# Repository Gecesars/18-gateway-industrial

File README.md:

# EDGE-18 — Gateway Industrial Modbus/CAN Universal

Plataforma-pai para aquisição industrial e telemetria dos demais projetos do
portfólio. O EDGE-18 lê Modbus RTU, quatro sinais 0–10 V/4–20 mA e quatro
entradas digitais/pulso, conserva dados offline e publica por MQTT/TLS.

> **Estado: revisão digital A congelada para documentação — não fabricar.**
> O esquemático passa no ERC, mas a PCB foi mantida no ponto solicitado pelo
> responsável: 43 ocorrências de DRC e 24 conexões abertas. Os arquivos servem
> para revisão de engenharia e continuidade do desenvolvimento; não constituem
> uma liberação fabril, protótipo validado ou produto certificado.

## Arquitetura P0

| Bloco | Seleção |
|---|---|
| MCU | STM32H563ZIT6, Cortex-M33/TrustZone |
| Ethernet | LAN8742Ai, RMII 10/100 |
| Wi-Fi | ESP32-C3-MINI-1 opcional |
| RS-485 | 2 × ISOW1412 isoladas |
| Analógicas | ADS8684, quatro canais de 16 bits |
| Digitais | 2 × ISO1212, quatro entradas de 24 V |
| CAN | ISO1042 reservado para fase 2 |
| Alimentação | 9–36 Vcc; LM76002 como referência |
| PCB | 180 × 120 mm, quatro camadas |

O MVP é somente de monitoramento. Não possui saídas de comando e não substitui
CLP ou relé de segurança.

## Entregue nesta revisão

- requisitos verificáveis e seis ADRs;
- esquemático KiCad A0 com sete blocos e ERC limpo;
- PCB KiCad de quatro camadas, 180 × 120 mm, com roteamento parcial congelado;
- trilhas de 0,25 a 1,20 mm, sem segmento abaixo de 0,25 mm;
- BOM de 181 posições, pinout de 144 pinos e cálculos elétricos;
- STEP atual da PCB e conjunto paramétrico FreeCAD;
- relatório DRC integral com as pendências conhecidas;
- arquitetura elétrica e de software;
- contratos de configuração e telemetria em JSON Schema;
- exemplos válidos;
- núcleo C17 testável com configuração, Modbus, scheduler, journal, telemetria,
  máquina de estados e manifesto de atualização;
- testes estritos no host e CI;
- quinze vistas técnicas e PDF consolidado.

## Evidência CAD — 15 vistas

Os recortes do esquemático foram exportados em alta resolução e ampliados por
bloco para preservar referências, valores e nomes de redes. As vistas da PCB
mostram deliberadamente o estado congelado, inclusive o roteamento ainda
incompleto.

| | | |
|---|---|---|
|  |  |  |
|  |  |  |
|  |  |  |
|  |  |  |
|  |  |  |

Documento consolidado: [EDGE-18 — projeto completo Rev. A](docs/EDGE-18-projeto-completo-rev-a.pdf).

## Verificação local

```bash
./tools/run-checks.sh
```

## Navegação

- [índice técnico](docs/README.md);
- [requisitos](docs/01-requisitos.md);
- [arquitetura](docs/02-arquitetura.md);
- [hardware](docs/03-hardware.md);
- [software](docs/04-software.md);
- [estado congelado da PCB Rev. A](docs/17-estado-da-pcb-rev-a.md);
- [relatório ERC](docs/reports/edge18-main-rev-a-erc.rpt);
- [relatório DRC](docs/reports/edge18-main-rev-a-drc.rpt);
- [fontes primárias](docs/12-fontes-primarias.md);
- [status](project-management/STATUS.md);
- [roadmap](project-management/ROADMAP.md).

## Licença

A licença ainda não foi definida. Não redistribua artefatos como se uma licença
já tivesse sido concedida.

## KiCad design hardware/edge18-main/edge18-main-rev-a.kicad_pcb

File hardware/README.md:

# Hardware

## Finalidade

Fontes de eletrônica do projeto.

## Entregáveis Rev. A

- `edge18-main/edge18-main-rev-a.kicad_sch`: esquemático A0 com sete blocos;
- `edge18-main/edge18-main-rev-a.kicad_pcb`: PCB 180 × 120 mm, quatro camadas;
- `libraries/frozen/`: símbolos resolvidos e congelados para ERC reprodutível;
- `bom/edge18-main-rev-a-source.csv`: 181 posições e quatro DNP;
- `scripts/generate_kicad.py`: fonte determinística de esquemático, PCB inicial
  e BOM;
- `scripts/generate_pinout.py`: tabela dos 144 pinos extraída do CAD;
- `scripts/specctra_io.py`: intercâmbio DSN/SES;
- relatórios ERC/DRC em `docs/reports/`.

## Regras principais

- trilha mínima global: 0,25 mm;
- padrão: 0,30 mm; analógico: 0,35 mm; campo: 0,50 mm;
- alimentação: 0,80 mm; VIN: 1,20 mm;
- quatro camadas: F.Cu, In1.Cu, In2.Cu e B.Cu;
- três rasgos sob as barreiras isoladas;
- ESP32-C3-WROOM-02 marcado DNP;
- nenhuma saída de controle de processo.

## Estado congelado

A PCB Rev. A foi congelada em 27 de julho de 2026 com 43 ocorrências de DRC e
24 conexões abertas, por decisão do responsável. Não retome o roteamento nem
gere arquivos fabris a partir desta baseline sem nova autorização. O
esquemático tem ERC limpo e não há trilha abaixo de 0,25 mm.

Detalhes: [`../docs/17-estado-da-pcb-rev-a.md`](../docs/17-estado-da-pcb-rev-a.md).

## Regeneração e validação de desenvolvimento

```bash
./tools/generate-hardware.sh
./tools/kicad-cli.sh sch erc \
  --exit-code-violations hardware/edge18-main/edge18-main-rev-a.kicad_sch
./tools/kicad-cli.sh pcb drc \
  --exit-code-violations hardware/edge18-main/edge18-main-rev-a.kicad_pcb
```

`generate-hardware.sh` substitui o PCB pelo posicionamento inicial; execute o
roteamento depois dele somente em uma futura linha de desenvolvimento
autorizada. `--schematic-only` atualiza esquemático, BOM e bibliotecas sem tocar
na PCB congelada; `--bom-only` atualiza somente a BOM.

## Limite da liberação

O ERC está limpo, mas o DRC não está. A revisão atual não pode ser fabricada.
Protótipo, DFM, bring-up, térmica, surto, EMC e isolamento também continuam
pendentes.

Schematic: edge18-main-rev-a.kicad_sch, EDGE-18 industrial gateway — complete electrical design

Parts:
BT1: CR1220; BatteryHolder_Keystone_3000_1x12mm; MPN 3000
C1: 100uF 63V; C_1210_3225Metric; MPN X7R industrial equivalent
C2: 1uF 100V X7R; C_1210_3225Metric; MPN X7R industrial equivalent
C3: 100nF 100V; C_0603_1608Metric; MPN C1608 X7R series
C4, C5: 10uF 16V; C_0603_1608Metric; MPN C1608 X7R series
C6: 4.7nF; C_0603_1608Metric; MPN C1608 X7R series
C7, C8: 22uF 10V; C_0603_1608Metric; MPN C1608 X7R series
C9: 10nF; C_0603_1608Metric; MPN C1608 X7R series
C10: 10uF 10V; C_0603_1608Metric; MPN C1608 X7R series
C11, C12, C13, C14: 12pF C0G; C_0603_1608Metric; MPN C1608 series
C15, C16, C17, C18, C19, C20, C21, C22, C26, C28, C29: 100nF; C_0603_1608Metric; MPN C1608 series
C23: 4.7uF; C_0603_1608Metric; MPN C1608 series
C24, C25: 2.2uF low-ESR; C_0603_1608Metric; MPN C1608 series
C27: 1uF; C_0603_1608Metric; MPN C1608 series
C30, C31, C32, C43, C44, C65, C84, C85, C90, C92: 100nF; C_0603_1608Metric
C33: 1uF 10V; C_0603_1608Metric; MPN C1608 X7R series
C40, C41: 12pF C0G; C_0603_1608Metric
C42: 1uF; C_0603_1608Metric
C45, C64: 10uF; C_0603_1608Metric
C46: 10uF; C_0805_2012Metric; not fitted
C60, C61, C62, C63: 10nF C0G; C_0603_1608Metric; MPN C1608C0G1H103J080AA
C66, C67: 10uF low-ESR; C_0603_1608Metric
C80, C81, C82, C83: 10nF 100V; C_1206_3216Metric; MPN C3216X7R2A103K160AA
C91, C93: 2.2uF 10V; C_0805_2012Metric
C94: 100nF; C_0805_2012Metric
C95: 2.2uF; C_0805_2012Metric
D1: SMBJ36A; D_SMB; MPN SMBJ36A
D2: SS56 60V/5A; D_SMB; MPN SS56-13-F
D3: RUN GREEN; LED_0603_1608Metric; MPN 0603 green LED
D4: FAULT RED; LED_0603_1608Metric; MPN 0603 red LED
D10, D11, D12, D13: SMAJ12A; D_SMA; MPN SMAJ12A
D14, D15, D16, D17: SMAJ33A; D_SMA; MPN SMAJ33A
D18, D19, D20: SM712; SOT-23; MPN SM712-02HTG
F1: 2A resettable; Fuse_1812_4532Metric; MPN 1812L200/33
FB1, FB2, FB3: 600R@100MHz; L_0603_1608Metric; MPN BLM18AG601SN1D
J1: POWER 9–36V / RETURN / CHASSIS; TerminalBlock_Phoenix_MKDS-1,5-3-5.08_1x03_P5.08mm_Horizont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; MPN 1715035 equivalent
J2: ARM SWD 10-pin; PinHeader_2x05_P1.27mm_Vertical_SMD; MPN FTSH-105-01-L-DV-K
J3: MICROSD INDUSTRIAL; microSD_HC_Molex_104031-0811; MPN 104031-0811
J4: USB-C SERVICE DEVICE; USB_C_Receptacle_GCT_USB4105-xx-A_16P_TopMnt_Horizontal; MPN USB4105-GF-A
J5: RJ45 MAGJACK 10/100; RJ45_Hanrun_HR911105A_Horizontal; MPN HR911105A
J6: SERVICE / EXPANSION; PinHeader_1x08_P2.54mm_Vertical
J10: AI1 / AGND; TerminalBlock_Phoenix_MKDS-1,5-2-5.08_1x02_P5.08mm_Horizont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; MPN MKDS 1,5/2-5,08
J11: AI2 / AGND; TerminalBlock_Phoenix_MKDS-1,5-2-5.08_1x02_P5.08mm_Horizont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; MPN MKDS 1,5/2-5,08
J12: AI3 / AGND; TerminalBlock_Phoenix_MKDS-1,5-2-5.08_1x02_P5.08mm_Horizont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; MPN MKDS 1,5/2-5,08
J13: AI4 / AGND; TerminalBlock_Phoenix_MKDS-1,5-2-5.08_1x02_P5.08mm_Horizont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; MPN MKDS 1,5/2-5,08
J14: DI1 / DI2 / DI3 / DI4 / FIELD COM; TerminalBlock_Phoenix_MKDS-1,5-5-5.08_1x05_P5.08mm_Horizont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; MPN MKDS 1,5/5-5,08
J15: RS-485 A: A+ / B- / ISO GND; TerminalBlock_Phoenix_MKDS-1,5-3-5.08_1x03_P5.08mm_Horizont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; MPN MKDS 1,5/3-5,08
J16: RS-485 B: A+ / B- / ISO GND; TerminalBlock_Phoenix_MKDS-1,5-3-5.08_1x03_P5.08mm_Horizont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; MPN MKDS 1,5/3-5,08
J17: CAN-H / CAN-L / ISO GND; TerminalBlock_Phoenix_MKDS-1,5-3-5.08_1x03_P5.08mm_Horizont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; MPN MKDS 1,5/3-5,08
JP1: AI1 CURRENT MODE; SolderJumper-2_P1.3mm_Open_Pad1.0x1.5mm
JP2: AI2 CURRENT MODE; SolderJumper-2_P1.3mm_Open_Pad1.0x1.5mm
JP3: AI3 CURRENT MODE; SolderJumper-2_P1.3mm_Open_Pad1.0x1.5mm
JP4: AI4 CURRENT MODE; SolderJumper-2_P1.3mm_Open_Pad1.0x1.5mm
JP5, JP6: 120R TERMINATION ENABLE; SolderJumper-2_P1.3mm_Open_Pad1.0x1.5mm
JP7: CAN 120R TERMINATION; SolderJumper-2_P1.3mm_Open_Pad1.0x1.5mm
L1: 10uH input EMI; L_12x12mm_H6mm; MPN SRP1265A-100M
L2: 10uH / 4.5A; L_10.4x10.4_H4.8; MPN XAL1010-103
L3: 2.2uH / 4A; L_6.3x6.3_H3; MPN XFL6030-222
R1: 40.2k 1%; R_0603_1608Metric; MPN RC0603FR series
R2: 10.0k 1%; R_0603_1608Metric; MPN RC0603FR series
R3: 150k 1%; R_0603_1608Metric; MPN RC0603FR series
R4, R15: 33k 1%; R_0603_1608Metric; MPN RC0603FR series
R5, R16, R19: 100k 1%; R_0603_1608Metric; MPN RC0603FR series
R6: 10k; R_0603_1608Metric; MPN RC0603FR series
R10: 10k; R_0603_1608Metric; MPN RC0603FR-0710KL
R11: 100k; R_0603_1608Metric; MPN RC0603FR-07100KL
R12, R13, R46, R47: 1k; R_0603_1608Metric
R14: 330k 1%; R_0603_1608Metric; MPN RC0603FR series
R17: 200k 1%; R_0603_1608Metric; MPN RC0603FR series
R18: 10k 1%; R_0603_1608Metric; MPN RC0603FR series
R20, R21: 4.7k; R_0603_1608Metric; MPN RC0603FR series
R22, R27, R28, R45, R91, R93, R95: 10k; R_0603_1608Metric
R23, R24: 5.1k; R_0603_1608Metric
R25: 100k; R_0603_1608Metric
R26: 33k; R_0603_1608Metric
R40: 12.1k 1%; R_0603_1608Metric
R41, R42, R43, R44: 49.9R 1%; R_0603_1608Metric
R48, R49: 10k; R_0603_1608Metric; not fitted
R60, R62, R64, R66: 249R 0.1% 25ppm; R_0805_2012Metric; MPN TNPW0805249RBEEN
R61, R63, R65, R67: 1k 0.1%; R_0603_1608Metric; MPN TNPW06031K00BEEA
R68: 0R star link; R_0805_2012Metric
R80, R82, R84, R86: 1.00k 1% RTHR; R_1206_3216Metric; MPN RC1206FR-071KL
R81, R83, R85, R87: 562R 1% RSENSE; R_1206_3216Metric; MPN RC1206FR-07562RL
R90, R92, R94: 120R 1%; R_1206_3216Metric
SW1: RESET; SW_SPST_TL3342; MPN TL3342F160QG
SW2: BOOT; SW_SPST_TL3342; MPN TL3342F160QG
U1: LM76002RNPR; Texas_RNP0030B_WQFN-30-1EP_4x6mm_P0.5mm_EP1.8x4.5mm_Thermal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; MPN LM76002RNPR
U2: TPS62132RGTR; VQFN-16-1EP_3x3mm_P0.5mm_EP1.68x1.68mm_ThermalVias; MPN TPS62132RGTR
U3: STM32H563ZIT6; LQFP-144_20x20mm_P0.5mm; MPN STM32H563ZIT6
U4: RV-3028-C7; MicroCrystal_C7_SON-8_1.5x3.2mm_P0.9mm; MPN RV-3028-C7
U5: W25Q128JVSIQ; SOIC-8_5.3x5.3mm_P1.27mm; MPN W25Q128JVSIQ
U6: USBLC6-2SC6; SOT-23-6; MPN USBLC6-2SC6
U7: LAN8742Ai-CZ-TR; VQFN-24-1EP_4x4mm_P0.5mm_EP2.5x2.5mm_ThermalVias; MPN LAN8742Ai-CZ-TR
U8: ESP32-C3-WROOM-02; MPN ESP32-C3-WROOM-02-N4; not fitted
U9: ADS8684IDBT; TSSOP-38_4.4x9.7mm_P0.5mm; MPN ADS8684IDBT
U10, U11: ISO1212DBQ; SSOP-16_3.9x4.9mm_P0.635mm; MPN ISO1212DBQ
U12, U13: ISOW1412DFMR; SOIC-20W_7.5x12.8mm_P1.27mm; MPN ISOW1412DFMR
U14: ISOW1044DFMR; SOIC-20W_7.5x12.8mm_P1.27mm; MPN ISOW1044DFMR
Y1: 25MHz 10pF; Crystal_SMD_3215-2Pin_3.2x1.5mm; MPN industrial crystal equivalent
Y2: 32.768kHz 12.5pF; Crystal_SMD_3215-2Pin_3.2x1.5mm; MPN industrial crystal equivalent
Y3: 25MHz 10pF; Crystal_SMD_3215-2Pin_3.2x1.5mm; MPN ABM8-25.000MHZ series

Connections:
3V3: C7.1, C8.1, C15.1, C16.1, C17.1, C18.1, C19.1, C20.1, C21.1, C22.1, C23.1, C30.1, C31.1, C43.1, C46.1, C84.1, C85.1, C90.1, C92.1, C94.1, FB1.1, FB2.1, J2.1, J3.4 (VDD), J5.10, J5.12, J6.1, L3.2, R10.1, R18.1, R20.1, R21.1, R22.1, R27.1, R28.1, R45.1, R48.1, R49.1, R91.1, R93.1, R95.1, SW2.2, U2.5 (FB), U2.14 (VOS), U3.17 (VDD), U3.30 (VDD), U3.39 (VDD), U3.52 (VDD), U3.62 (VDD), U3.72 (VDD), U3.84 (VDD), U3.95 (VDD), U3.106 (VDDUSB), U3.108 (VDD), U3.121 (VDDIO2), U3.131 (VDD), U3.144 (VDD), U4.7 (VDD), U5.8 (VCC), U7.9 (VDDIO), U8.1 (3V3), U9.34 (DVDD), U10.2 (VCC1), U10.3 (EN), U11.2 (VCC1), U11.3 (EN), U12.1 (VIO), U13.1 (VIO), U14.1 (VIO)
3V3_A: C26.1, C27.1, FB1.2, U3.32 (VREF+), U3.33 (VDDA)
3V3_ETH: C44.1, C45.1, FB2.2, J5.4 (TCT), J5.5 (RCT), R41.1, R42.1, R43.1, R44.1, U7.1 (VDD2A), U7.19 (VDD1A)
3V3_MON: R18.2, R19.1, U3.29 (PC3)
3V3_RTC: BT1.1 (+), C28.1, U3.6 (VBAT), U4.6 (VBACKUP)
5V: C4.1, C5.1, C10.1, FB3.1, L2.2, R1.1, R6.1, R16.1, U1.9 (BIAS), U2.10 (VIN), U2.11 (VIN), U2.12 (VIN), U2.13 (EN), U12.9 (VDD), U13.9 (VDD), U14.9 (VDD)
5V_A: C64.1, C65.1, FB3.2, U9.9 (AVDD), U9.30 (AVDD)
5V_MON: R16.2, R17.1, U3.28 (PC2)
ADC_CS: U3.40 (PA4), U9.38 (~CS)
ADC_MISO: U3.42 (PA6), U9.36 (SDO)
ADC_MOSI: U3.135 (PB5), U9.1 (SDI)
ADC_REFCAP: C66.1, U9.7 (REFCAP)
ADC_REFIO: C67.1, U9.5 (REFIO)
ADC_RESET: U3.46 (PB0), U9.2 (~RST/PD)
ADC_SCK: U3.41 (PA5), U9.37 (SCLK)
AGND: C26.2, C27.2, C60.2, C61.2, C62.2, C63.2, C64.2, C65.2, C66.2, C67.2, D10.2 (A2), D11.2 (A2), D12.2 (A2), D13.2 (A2), J10.2, J11.2, J12.2, J13.2, R60.2, R62.2, R64.2, R66.2, R68.1, U3.31 (VSSA), U9.6 (REFGND), U9.8 (AGND), U9.11 (AUX_GND), U9.17 (AIN_0GND), U9.19 (AIN_1GND), U9.20 (AIN_2GND), U9.22 (AIN_3GND), U9.28 (AGND), U9.29 (AGND), U9.31 (AGND), U9.32 (AGND)
AI1_ADC: C60.1, R61.2, U9.16 (AIN_0P)
AI1_FIELD: D10.1 (A1), J10.1, JP1.1 (A), R61.1
AI1_SHUNT: JP1.2 (B), R60.1
AI2_ADC: C61.1, R63.2, U9.18 (AIN_1P)
AI2_FIELD: D11.1 (A1), J11.1, JP2.1 (A), R63.1
AI2_SHUNT: JP2.2 (B), R62.1
AI3_ADC: C62.1, R65.2, U9.21 (AIN_2P)
AI3_FIELD: D12.1 (A1), J12.1, JP3.1 (A), R65.1
AI3_SHUNT: JP3.2 (B), R64.1
AI4_ADC: C63.1, R67.2, U9.23 (AIN_3P)
AI4_FIELD: D13.1 (A1), J13.1, JP4.1 (A), R67.1
AI4_SHUNT: JP4.2 (B), R66.1
BOOT0: R11.1, SW2.1, U3.138 (BOOT0)
BOOT_5V: C3.1, U1.6 (BOOT)
CAN_EN: R95.2, U14.8 (EN/FLT)
CAN_GND: C95.2, D20.3 (common), J17.3, U14.11 (GND2), U14.15 (GISOIN), U14.16 (GISOIN), U14.17 (GISOIN)
CAN_H: D20.1 (A1), J17.1, JP7.1 (A), U14.19 (CANH)
CAN_L: D20.2 (A2), J17.2, R94.2, U14.18 (CANL)
CAN_RX: U3.114 (PD0), U14.5 (RXD)
CAN_STB: U3.117 (PD3), U14.4 (STB)
CAN_TERM: JP7.2 (B), R94.1
CAN_TX: U3.115 (PD1), U14.3 (TXD)
CAN_VISO: C95.1, U14.12 (VISOOUT), U14.13 (VSIN), U14.20 (VISOIN)
CHASSIS: J1.3, J3.10 (SHIELD), J4.S1 (SHIELD), J5.8, J5.SH
DI1: U3.4 (PE5), U10.4 (OUT1)
DI1_FIELD: D14.1 (A1), J14.1, R80.1
DI1_IN: R81.2, U10.15 (IN1)
DI1_SENSE: C80.1, R80.2, R81.1, U10.16 (SENSE1)
DI2: U3.5 (PE6), U10.5 (OUT2)
DI2_FIELD: D15.1 (A1), J14.2, R82.1
DI2_IN: R83.2, U10.10 (IN2)
DI2_SENSE: C81.1, R82.2, R83.1, U10.11 (SENSE2)
DI3: U3.60 (PE9), U11.4 (OUT1)
DI3_FIELD: D16.1 (A1), J14.3, R84.1
DI3_IN: R85.2, U11.15 (IN1)
DI3_SENSE: C82.1, R84.2, R85.1, U11.16 (SENSE1)
DI4: U3.64 (PE11), U11.5 (OUT2)
DI4_FIELD: D17.1 (A1), J14.4, R86.1
DI4_IN: R87.2, U11.10 (IN2)
DI4_SENSE: C83.1, R86.2, R87.1, U11.11 (SENSE2)
DI_FIELD_GND: C80.2, C81.2, C82.2, C83.2, D14.2 (A2), D15.2 (A2), D16.2 (A2), D17.2 (A2), J14.5, U10.9 (FGND2), U10.12 (SUB2), U10.13 (SUB1), U10.14 (FGND1), U11.9 (FGND2), U11.12 (SUB2), U11.13 (SUB1), U11.14 (FGND1)
EN_5V: R3.2, R4.1, U1.18 (EN)
ETH_CRS_DV: U3.43 (PA7), U7.11 (CRS_DV/MODE2)
ETH_LED1: R46.1, U7.3 (LED1/REGOFF)
ETH_LED1_K: J5.11, R46.2
ETH_LED2: R47.1, U7.2 (LED2/~INTSEL)
ETH_LED2_K: J5.9, R47.2
ETH_MDC: U3.27 (PC1), U7.13 (MDC)
ETH_MDIO: U3.36 (PA2), U7.12 (MDIO)
ETH_PHY_RESET: R45.2, U7.15 (~RST)
ETH_RBIAS: R40.1, U7.24 (RBIAS)
ETH_REF_CLK: U3.35 (PA1), U7.14 (~INT/REFCLKO)
ETH_RXD0: U3.44 (PC4), U7.8 (RXD0/MODE0)
ETH_RXD1: U3.45 (PC5), U7.7 (RXD1/MODE1)
ETH_RX_N: J5.6 (RD-), R44.2, U7.22 (RXN)
ETH_RX_P: J5.3 (RD+), R43.2, U7.23 (RXP)
ETH_TXD0: U3.128 (PG13), U7.17 (TXD0)
ETH_TXD1: U3.129 (PG14), U7.18 (TXD1)
ETH_TX_EN: U3.126 (PG11), U7.16 (TXEN)
ETH_TX_N: J5.2 (TD-), R42.2, U7.20 (TXN)
ETH_TX_P: J5.1 (TD+), R41.2, U7.21 (TXP)
ETH_VDDCR: C42.1, U7.6 (VDDCR)
ETH_XTAL_IN: C40.1, U7.5 (XTAL1/CLKIN), Y3.1
ETH_XTAL_OUT: C41.1, U7.4 (XTAL2), Y3.2
EXP_GPIO: J6.7, U3.123 (PD7)
EXP_UART_TX: J6.5, U3.69 (PB10)
FB_5V: R1.2, R2.1, U1.12 (FB)
FLASH_CS: U3.73 (PB12), U5.1 (~CS)
FLASH_HOLD: R28.2, U5.7 (~HOLD/~RESET/IO_{3})
FLASH_MISO: U3.75 (PB14), U5.2 (DO/IO_{1})
FLASH_MOSI: U3.76 (PB15), U5.5 (DI/IO_{0})
FLASH_SCK: U3.74 (PB13), U5.6 (CLK)
FLASH_WP: R27.2, U5.3 (~WP/IO_{2})
GND: BT1.2 (-), C1.2, C2.2, C4.2, C5.2, C6.2, C7.2, C8.2, C9.2, C10.2, C11.2, C12.2, C13.2, C14.2, C15.2, C16.2, C17.2, C18.2, C19.2, C20.2, C21.2, C22.2, C23.2, C24.2, C25.2, C28.2, C29.2, C30.2, C31.2, C32.2, C33.2, C40.2, C41.2, C42.2, C43.2, C44.2, C45.2, C46.2, C84.2, C85.2, C90.2, C92.2, C94.2, D1.2 (A2), D3.2 (A), D4.2 (A), J1.2, J2.3, J2.5, J2.9, J3.6 (VSS), J4.A1 (GND), J4.A12 (GND), J4.B1 (GND), J4.B12 (GND), J6.2, R2.2, R4.2, R5.2, R11.2, R15.2, R17.2, R19.2, R23.2, R24.2, R26.2, R40.2, R68.2, SW1.2, U1.13 (AGND), U1.14 (AGND), U1.15 (AGND), U1.17 (SYNC/MODE), U1.19 (NC_{GND}), U1.24 (PGND), U1.25 (PGND), U1.26 (PGND), U1.27 (NC_{GND}), U1.28 (NC_{GND}), U1.29 (NC_{GND}), U1.30 (NC_{GND}), U1.31 (AGND), U2.6 (GND), U2.7 (FSW), U2.8 (DEF), U2.15 (GND), U2.16 (GND), U2.17 (GND), U3.16 (VSS), U3.38 (VSS), U3.51 (VSS), U3.61 (VSS), U3.71 (VSS), U3.83 (VSS), U3.94 (VSS), U3.107 (VSS), U3.120 (VSS), U3.130 (VSS), U3.143 (VSS), U4.5 (VSS), U4.8 (EVI), U5.4 (GND), U6.2 (GND), U7.25 (VSS), U8.9 (GND), U8.19 (GND), U9.3 (DAISY), U9.4 (~REFSEL), U9.33 (DGND), U10.1 (GND1), U10.8 (GND1), U11.1 (GND1), U11.8 (GND1), U12.6 (GNDIO), U12.10 (GND1), U13.6 (GNDIO), U13.10 (GND1), U14.2 (IN), U14.6 (GNDIO), U14.10 (GND1)
HSE_IN: C11.1, U3.23 (PH0), Y1.1
HSE_OUT: C12.1, U3.24 (PH1), Y1.2
I2C_SCL: J6.3, R20.2, U3.139 (PB8), U4.3 (SCL)
I2C_SDA: J6.4, R21.2, U3.140 (PB9), U4.4 (SDA)
LED_FAULT: R13.1, U3.57 (PG1)
LED_FAULT_A: D4.1 (K), R13.2
LED_RUN: R12.1, U3.56 (PG0)
LED_RUN_A: D3.1 (K), R12.2
LSE_IN: C13.1, U3.8 (PC14), Y2.1
LSE_OUT: C14.1, U3.9 (PC15), Y2.2
NRST: C29.1, J2.10, J6.8, R10.2, SW1.1, U3.25 (NRST)
PGOOD_3V3: U2.4 (PG), U3.87 (PG2)
PGOOD_5V: R6.2, U1.16 (PGOOD), U3.88 (PG3)
RS485A_DIR: U3.118 (PD4), U12.3 (DE), U12.5 (~RE)
RS485A_EN: R91.2, U12.8 (EN/FLT)
RS485A_GND: C91.2, D18.3 (common), J15.3, U12.11 (GND2), U12.13 (MODE), U12.15 (GISOIN)
RS485A_N: D18.2 (A2), J15.2, R90.2, U12.18 (Z), U12.19 (B)
RS485A_P: D18.1 (A1), J15.1, JP5.1 (A), U12.17 (Y), U12.20 (A)
RS485A_RX: U3.122 (PD6), U12.4 (R)
RS485A_TERM: JP5.2 (B), R90.1
RS485A_TX: U3.119 (PD5), U12.2 (D)
RS485A_VISO: C91.1, U12.12 (VISOOUT), U12.16 (VISOIN)
RS485B_DIR: U3.81 (PD12), U13.3 (DE), U13.5 (~RE)
RS485B_EN: R93.2, U13.8 (EN/FLT)
RS485B_GND: C93.2, D19.3 (common), J16.3, U13.11 (GND2), U13.13 (MODE), U13.15 (GISOIN)
RS485B_N: D19.2 (A2), J16.2, R92.2, U13.18 (Z), U13.19 (B)
RS485B_P: D19.1 (A1), J16.1, JP6.1 (A), U13.17 (Y), U13.20 (A)
RS485B_RX: U3.78 (PD9), U13.4 (R)
RS485B_TERM: JP6.2 (B), R92.1
RS485B_TX: U3.77 (PD8), U13.2 (D)
RS485B_VISO: C93.1, U13.12 (VISOOUT), U13.16 (VISOIN)
RTC_INT: U3.10 (PF0), U4.2 (~INT)
RT_5V: R5.1, U1.10 (RT)
SD_CLK: J3.5 (CLK), U3.113 (PC12)
SD_CMD: J3.3 (CMD), U3.116 (PD2)
SD_D0: J3.7 (DAT0), U3.98 (PC8)
SD_D1: J3.8 (DAT1), U3.99 (PC9)
SD_D2: J3.1 (DAT2), U3.111 (PC10)
SD_D3: J3.2 (DAT3/CD), U3.112 (PC11)
SD_DETECT: J3.9 (DET), R22.2
SS_3V3: C9.1, U2.9 (SS/TR)
SS_5V: C6.1, U1.11 (SS/TRK)
SWCLK: J2.4, U3.109 (PA14(JTCK)
SWDIO: J2.2, U3.105 (PA13(JTMS)
SWO: J2.6, U3.133 (PB3(JTDO)
SW_3V3: L3.1, U2.1 (SW), U2.2 (SW), U2.3 (SW)
SW_5V: C3.2, L2.1, U1.1 (SW), U1.2 (SW), U1.3 (SW), U1.4 (SW), U1.5 (SW)
USB_CC1: J4.A5 (CC1), R23.1
USB_CC2: J4.B5 (CC2), R24.1
USB_DM: U3.103 (PA11), U6.6 (I/O1)
USB_DM_RAW: J4.A7 (D-), J4.B7 (D-), U6.1 (I/O1)
USB_DP: U3.104 (PA12), U6.4 (I/O2)
USB_DP_RAW: J4.A6 (D+), J4.B6 (D+), U6.3 (I/O2)
USB_VBUS: J4.A4 (VBUS), J4.A9 (VBUS), J4.B4 (VBUS), J4.B9 (VBUS), R25.1, U6.5 (VBUS)
USB_VBUS_SENSE: C32.1, R25.2, R26.1, U3.101 (PA9)
VCAP1: C24.1, U3.70 (VCAP)
VCAP2: C25.1, U3.142 (VCAP)
VCC_5V: C33.1, U1.8 (VCC)
VIN_FILTERED: C1.1, C2.1, L1.2, R3.1, R14.1, U1.20 (PVIN), U1.21 (PVIN), U1.22 (PVIN)
VIN_FUSED: D1.1 (A1), D2.1 (K), F1.2
VIN_MON: R14.2, R15.1, U3.26 (PC0)
VIN_PROTECTED: D2.2 (A), L1.1
VIN_RAW: F1.1, J1.1
WIFI_BOOT: R49.2, U3.66 (PE13), U8.8 (IO9)
WIFI_EN: R48.2, U3.63 (PE10), U8.2 (EN)
WIFI_UART_RX: J6.6, U3.58 (PE7), U8.12 (IO21/TXD)
WIFI_UART_TX: U3.59 (PE8), U8.11 (IO20/RXD)

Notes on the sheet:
1 — POWER INPUT, PROTECTION AND REGULATION (9–36 VDC)
2 — SECURE CONTROLLER, CLOCKS, DEBUG AND SUPERVISION
3 — RTC, FLASH, MICROSD AND USB-C SERVICE
4 — ETHERNET 10/100 RMII AND OPTIONAL WI-FI COPROCESSOR
5 — FOUR 0–10 V / 4–20 mA ANALOG INPUTS
6 — FOUR ISOLATED IEC 61131-2 TYPE 3 DIGITAL INPUTS
7 — TWO ISOLATED RS-485 PORTS AND ISOLATED CAN-FD
DESIGN LIMITS: monitoring only; no safety outputs; close current-mode jumpers only for 4–20 mA.
Isolation barriers and chassis bonding must be reviewed against the installation category before field deployment.

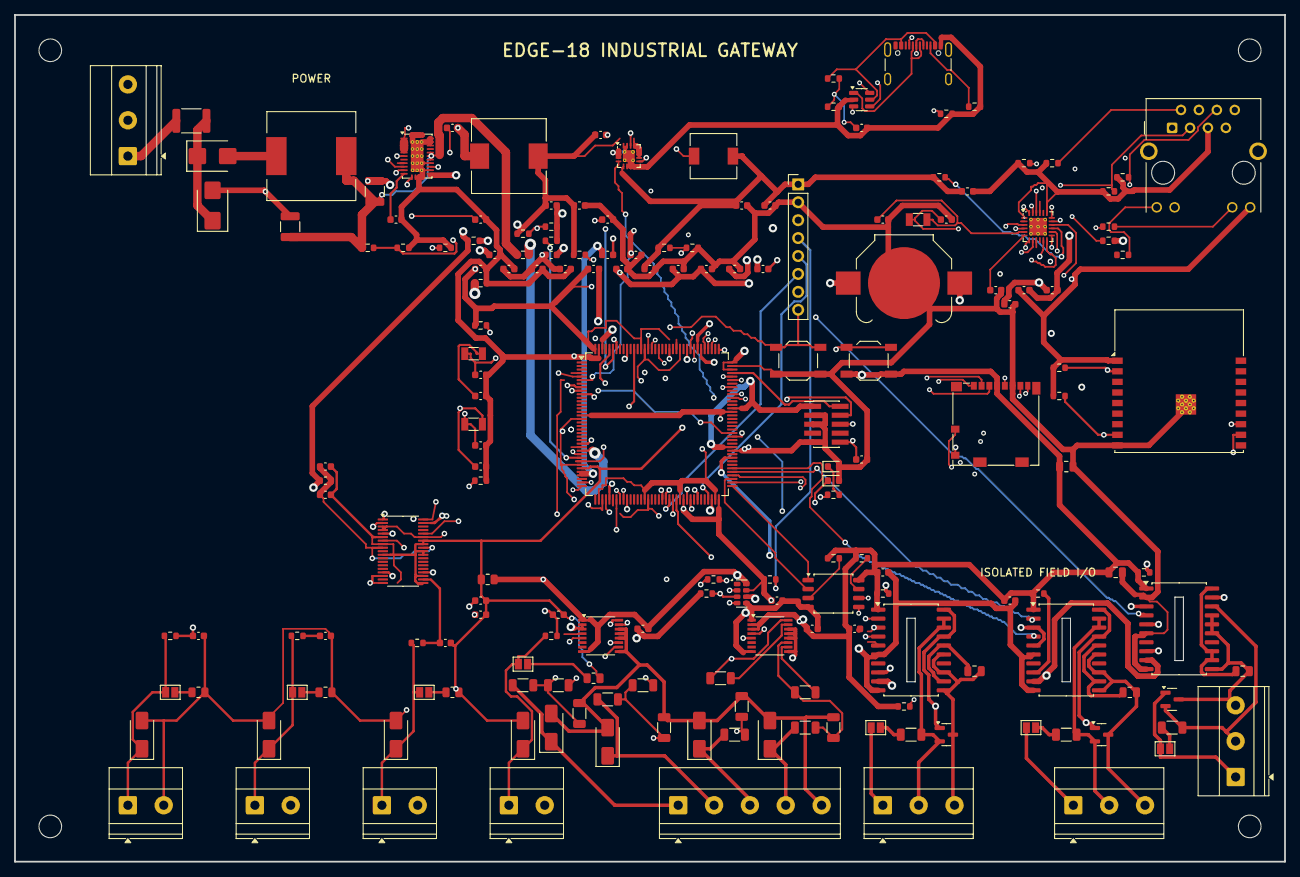
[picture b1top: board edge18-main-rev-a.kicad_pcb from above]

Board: 4 copper layers, 180.0 x 120.0 mm, 185 parts (0 on the bottom side), 157 nets.

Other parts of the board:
H1, H3, H4, H6: MountingHole_3.2mm_M3

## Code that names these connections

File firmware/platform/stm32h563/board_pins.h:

#ifndef EDGE18_STM32H563_BOARD_PINS_H
#define EDGE18_STM32H563_BOARD_PINS_H

/*
 * Single firmware-side source for the Rev. A signal assignment. The net and
 * physical pin are generated in docs/13-pinout-stm32h563-rev-a.md from KiCad;
 * changing this map requires changing and revalidating the native CAD.
 */
#define EDGE18_BOARD_SIGNAL_MAP(X) \
    X(DI1,              E,  5, "TIM/GPIO input") \
    X(DI2,              E,  6, "TIM/GPIO input") \
    X(RTC_INT,          F,  0, "EXTI input") \
    X(VIN_MON,          C,  0, "ADC input") \
    X(ETH_MDC,          C,  1, "ETH MDC") \
    X(MON_5V,           C,  2, "ADC input") \
    X(MON_3V3,          C,  3, "ADC input") \
    X(ETH_REF_CLK,      A,  1, "ETH RMII") \
    X(ETH_MDIO,         A,  2, "ETH MDIO") \
    X(ADC_CS,           A,  4, "GPIO output") \
    X(ADC_SCK,          A,  5, "SPI1 SCK") \
    X(ADC_MISO,         A,  6, "SPI1 MISO") \
    X(ETH_CRS_DV,       A,  7, "ETH RMII") \
    X(ETH_RXD0,         C,  4, "ETH RMII") \
    X(ETH_RXD1,         C,  5, "ETH RMII") \
    X(ADC_RESET,        B,  0, "GPIO output") \
    X(LED_RUN,          G,  0, "GPIO output") \
    X(LED_FAULT,        G,  1, "GPIO output") \
    X(WIFI_UART_RX,     E,  7, "UART7 RX") \
    X(WIFI_UART_TX,     E,  8, "UART7 TX") \
    X(DI3,              E,  9, "TIM/GPIO input") \
    X(WIFI_EN,          E, 10, "GPIO output") \
    X(DI4,              E, 11, "TIM/GPIO input") \
    X(WIFI_BOOT,        E, 13, "GPIO output") \
    X(EXP_UART_TX,      B, 10, "USART3 TX / expansion") \
    X(FLASH_CS,         B, 12, "GPIO output") \
    X(FLASH_SCK,        B, 13, "SPI2 SCK") \
    X(FLASH_MISO,       B, 14, "SPI2 MISO") \
    X(FLASH_MOSI,       B, 15, "SPI2 MOSI") \
    X(RS485B_TX,        D,  8, "USART3 TX") \
    X(RS485B_RX,        D,  9, "USART3 RX") \
    X(RS485B_DIR,       D, 12, "USART3 DE") \
    X(PGOOD_3V3,        G,  2, "EXTI input") \
    X(PGOOD_5V,         G,  3, "EXTI input") \
    X(SD_D0,            C,  8, "SDMMC1 D0") \
    X(SD_D1,            C,  9, "SDMMC1 D1") \
    X(USB_VBUS_SENSE,   A,  9, "USB FS VBUS") \
    X(USB_DM,           A, 11, "USB FS DM") \
    X(USB_DP,           A, 12, "USB FS DP") \
    X(SWDIO,            A, 13, "SWDIO") \
    X(SWCLK,            A, 14, "SWCLK") \
    X(SD_D2,            C, 10, "SDMMC1 D2") \
    X(SD_D3,            C, 11, "SDMMC1 D3") \
    X(SD_CLK,           C, 12, "SDMMC1 CK") \
    X(CAN_RX,           D,  0, "FDCAN1 RX") \
    X(CAN_TX,           D,  1, "FDCAN1 TX") \
    X(SD_CMD,           D,  2, "SDMMC1 CMD") \
    X(CAN_STB,          D,  3, "GPIO output") \
    X(RS485A_DIR,       D,  4, "USART2 DE") \
    X(RS485A_TX,        D,  5, "USART2 TX") \
    X(RS485A_RX,        D,  6, "USART2 RX") \
    X(EXP_GPIO,         D,  7, "GPIO expansion") \
    X(ETH_TX_EN,        G, 11, "ETH RMII") \
    X(ETH_TXD0,         G, 13, "ETH RMII") \
    X(ETH_TXD1,         G, 14, "ETH RMII") \
    X(SWO,              B,  3, "SWO") \
    X(ADC_MOSI,         B,  5, "SPI1 MOSI") \
    X(I2C_SCL,          B,  8, "I2C1 SCL") \
    X(I2C_SDA,          B,  9, "I2C1 SDA")

#define EDGE18_HSE_HZ 25000000UL
#define EDGE18_LSE_HZ 32768UL
#define EDGE18_SYSTEM_CLOCK_HZ 250000000UL
#define EDGE18_WATCHDOG_WINDOW_MS 2000UL

#endif
